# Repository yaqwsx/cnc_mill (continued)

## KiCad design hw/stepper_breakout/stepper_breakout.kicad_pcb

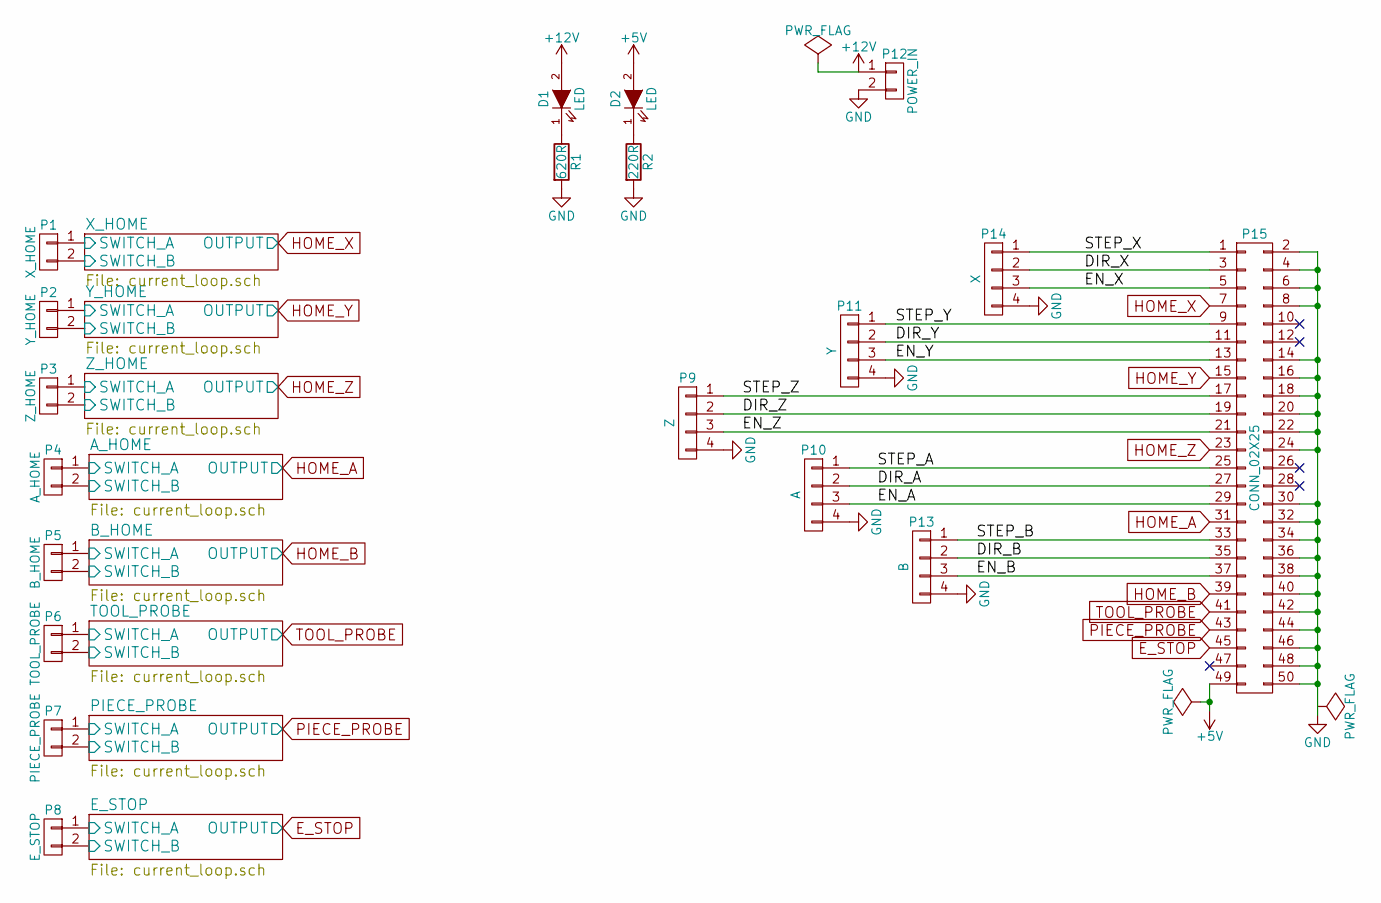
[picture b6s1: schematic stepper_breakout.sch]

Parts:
D1, D2: LED; LED_1206
P1: X_HOME; TerminalBlock_Pheonix_MKDS1.5-2pol
P2: Y_HOME; TerminalBlock_Pheonix_MKDS1.5-2pol
P3: Z_HOME; TerminalBlock_Pheonix_MKDS1.5-2pol
P4: A_HOME; TerminalBlock_Pheonix_MKDS1.5-2pol
P5: B_HOME; TerminalBlock_Pheonix_MKDS1.5-2pol
P6: TOOL_PROBE; TerminalBlock_Pheonix_MKDS1.5-2pol
P7: PIECE_PROBE; TerminalBlock_Pheonix_MKDS1.5-2pol
P8: E_STOP; TerminalBlock_Pheonix_MKDS1.5-2pol
P9: Z; TerminalBlock_Pheonix_MKDS1.5-4pol
P10: A; TerminalBlock_Pheonix_MKDS1.5-4pol
P11: Y; TerminalBlock_Pheonix_MKDS1.5-4pol
P12: POWER_IN; TerminalBlock_Pheonix_MKDS1.5-2pol
P13: B; TerminalBlock_Pheonix_MKDS1.5-4pol
P14: X; TerminalBlock_Pheonix_MKDS1.5-4pol
P15: CONN_02X25; IDC_Header_Straight_50pins
R1: 620R; R_0603
R2: 220R; R_0603

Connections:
+5V: D2.2 (A), P15.49
+12V: D1.2 (A), P12.1; also elsewhere on the board
/A_HOME/SWITCH_A: P4.1; also elsewhere on the board
/A_HOME/SWITCH_B: P4.2; also elsewhere on the board
/B_HOME/SWITCH_A: P5.1; also elsewhere on the board
/B_HOME/SWITCH_B: P5.2; also elsewhere on the board
/DIR_A: P10.2, P15.27
/DIR_B: P13.2, P15.35
/DIR_X: P14.2, P15.3
/DIR_Y: P11.2, P15.11
/DIR_Z: P9.2, P15.19
/EN_A: P10.3, P15.29
/EN_B: P13.3, P15.37
/EN_X: P14.3, P15.5
/EN_Y: P11.3, P15.13
/EN_Z: P9.3, P15.21
/E_STOP/SWITCH_A: P8.1; also elsewhere on the board
/E_STOP/SWITCH_B: P8.2; also elsewhere on the board
/PIECE_PROBE/SWITCH_A: P7.1; also elsewhere on the board
/PIECE_PROBE/SWITCH_B: P7.2; also elsewhere on the board
/STEP_A: P10.1, P15.25
/STEP_B: P13.1, P15.33
/STEP_X: P14.1, P15.1
/STEP_Y: P11.1, P15.9
/STEP_Z: P9.1, P15.17
/TOOL_PROBE/SWITCH_A: P6.1; also elsewhere on the board
/TOOL_PROBE/SWITCH_B: P6.2; also elsewhere on the board
/X_HOME/SWITCH_A: P1.1; also elsewhere on the board
/X_HOME/SWITCH_B: P1.2; also elsewhere on the board
/Y_HOME/SWITCH_A: P2.1; also elsewhere on the board
/Y_HOME/SWITCH_B: P2.2; also elsewhere on the board
/Z_HOME/SWITCH_A: P3.1; also elsewhere on the board
/Z_HOME/SWITCH_B: P3.2; also elsewhere on the board
E_STOP: P15.45; also elsewhere on the board
GND: P9.4, P10.4, P11.4, P12.2, P13.4, P14.4, P15.2, P15.4, P15.6, P15.8, P15.14, P15.16, P15.18, P15.20, P15.22, P15.24, P15.30, P15.32, P15.34, P15.36, P15.38, P15.40, P15.42, P15.44, P15.46, P15.48, P15.50, R1.2, R2.2; also elsewhere on the board
HOME_A: P15.31; also elsewhere on the board
HOME_B: P15.39; also elsewhere on the board
HOME_X: P15.7; also elsewhere on the board
HOME_Y: P15.15; also elsewhere on the board
HOME_Z: P15.23; also elsewhere on the board
unnamed: D1.1 (K), R1.1
unnamed: D2.1 (K), R2.1
PIECE_PROBE: P15.43; also elsewhere on the board
TOOL_PROBE: P15.41; also elsewhere on the board

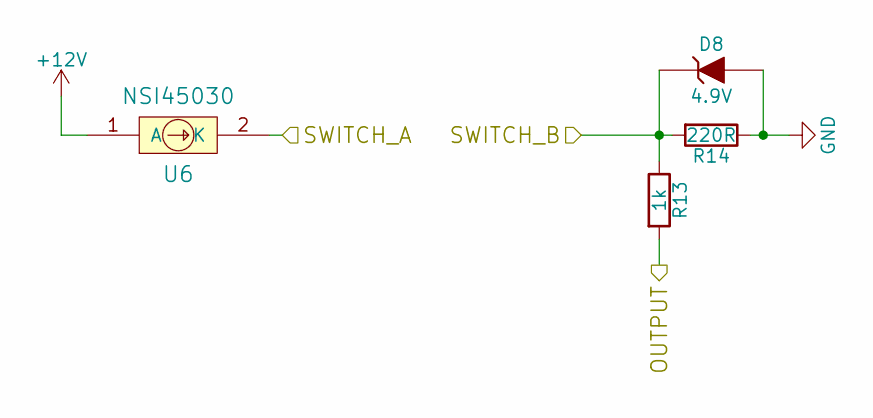
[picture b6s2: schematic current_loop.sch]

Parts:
D3: 4.9V; MELF_Standard
R3: 1k; R_0603_HandSoldering
R4: 220R; R_0603_HandSoldering
U1: NSI45030; SOD-123

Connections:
+12V: U1.1 (A); also elsewhere on the board
/Y_HOME/SWITCH_A: U1.2 (K); also elsewhere on the board
/Y_HOME/SWITCH_B: D3.1 (K), R3.1, R4.2; also elsewhere on the board
GND: D3.2 (A), R4.1; also elsewhere on the board
HOME_Y: R3.2; also elsewhere on the board

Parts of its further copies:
D4, D5, D6, D7, D8, D9, D10: 4.9V; MELF_Standard
R5, R7, R9, R11, R13, R15, R17: 1k; R_0603_HandSoldering
R6, R8, R10, R12, R14, R16, R18: 220R; R_0603_HandSoldering
U2, U3, U4, U5, U6, U7, U8: NSI45030; SOD-123

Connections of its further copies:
+12V: U2.1 (A), U3.1 (A), U4.1 (A), U5.1 (A), U6.1 (A), U7.1 (A), U8.1 (A); also elsewhere on the board
/A_HOME/SWITCH_A: U3.2 (K); also elsewhere on the board
/A_HOME/SWITCH_B: D5.1 (K), R7.1, R8.2; also elsewhere on the board
/B_HOME/SWITCH_A: U4.2 (K); also elsewhere on the board
/B_HOME/SWITCH_B: D6.1 (K), R9.1, R10.2; also elsewhere on the board
/E_STOP/SWITCH_A: U7.2 (K); also elsewhere on the board
/E_STOP/SWITCH_B: D9.1 (K), R15.1, R16.2; also elsewhere on the board
/PIECE_PROBE/SWITCH_A: U6.2 (K); also elsewhere on the board
/PIECE_PROBE/SWITCH_B: D8.1 (K), R13.1, R14.2; also elsewhere on the board
/TOOL_PROBE/SWITCH_A: U5.2 (K); also elsewhere on the board
/TOOL_PROBE/SWITCH_B: D7.1 (K), R11.1, R12.2; also elsewhere on the board
/X_HOME/SWITCH_A: U8.2 (K); also elsewhere on the board
/X_HOME/SWITCH_B: D10.1 (K), R17.1, R18.2; also elsewhere on the board
/Z_HOME/SWITCH_A: U2.2 (K); also elsewhere on the board
/Z_HOME/SWITCH_B: D4.1 (K), R5.1, R6.2; also elsewhere on the board
E_STOP: R15.2; also elsewhere on the board
GND: D4.2 (A), D5.2 (A), D6.2 (A), D7.2 (A), D8.2 (A), D9.2 (A), D10.2 (A), R6.1, R8.1, R10.1, R12.1, R14.1, R16.1, R18.1; also elsewhere on the board
HOME_A: R7.2; also elsewhere on the board
HOME_B: R9.2; also elsewhere on the board
HOME_X: R17.2; also elsewhere on the board
HOME_Z: R5.2; also elsewhere on the board
PIECE_PROBE: R13.2; also elsewhere on the board
TOOL_PROBE: R11.2; also elsewhere on the board

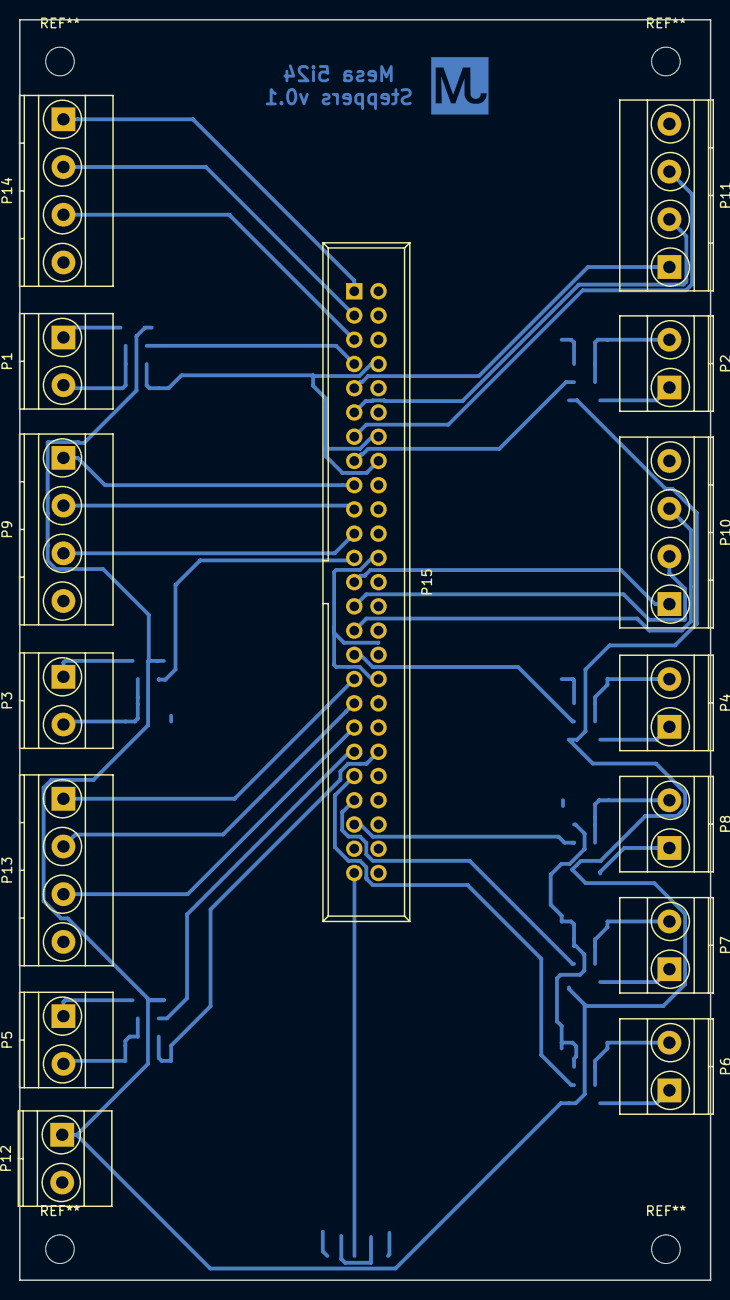
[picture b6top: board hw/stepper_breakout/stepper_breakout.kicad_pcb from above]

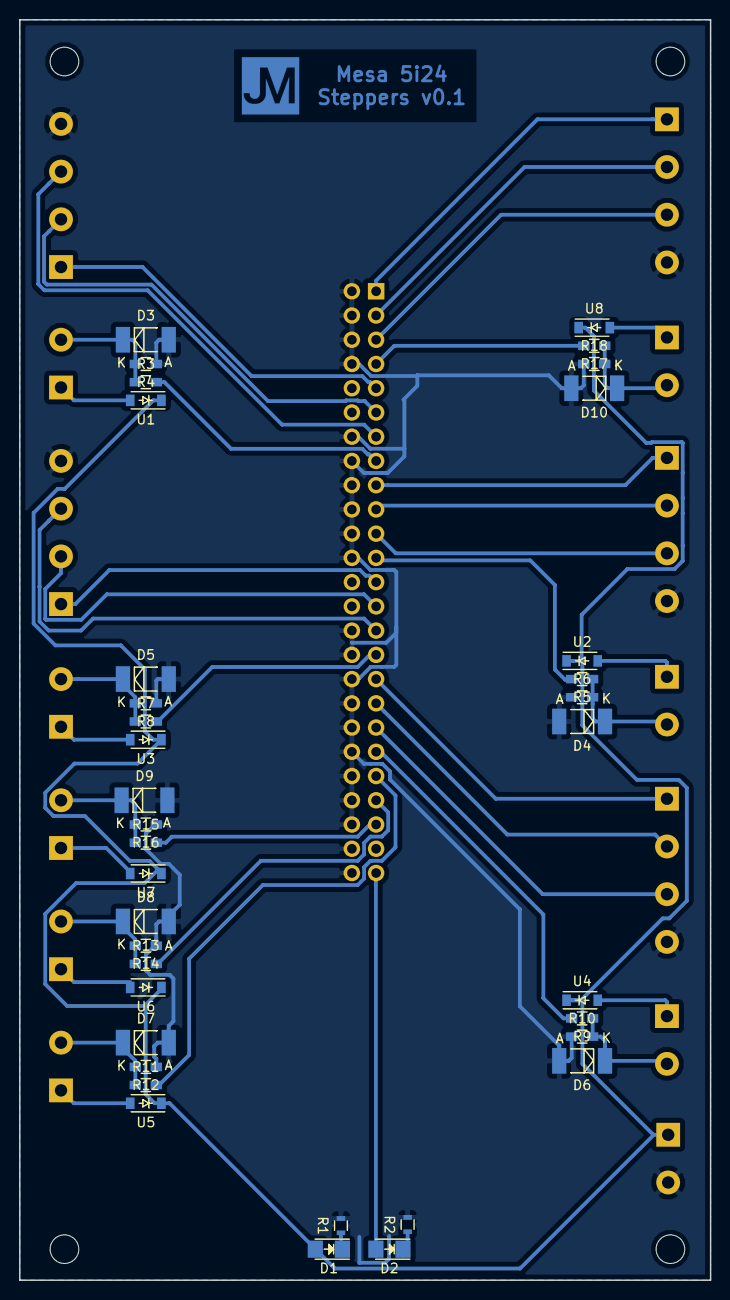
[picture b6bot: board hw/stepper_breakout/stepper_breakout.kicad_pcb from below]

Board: 2 copper layers, 72.4 x 132.1 mm, 51 parts (36 on the bottom side), 44 nets.

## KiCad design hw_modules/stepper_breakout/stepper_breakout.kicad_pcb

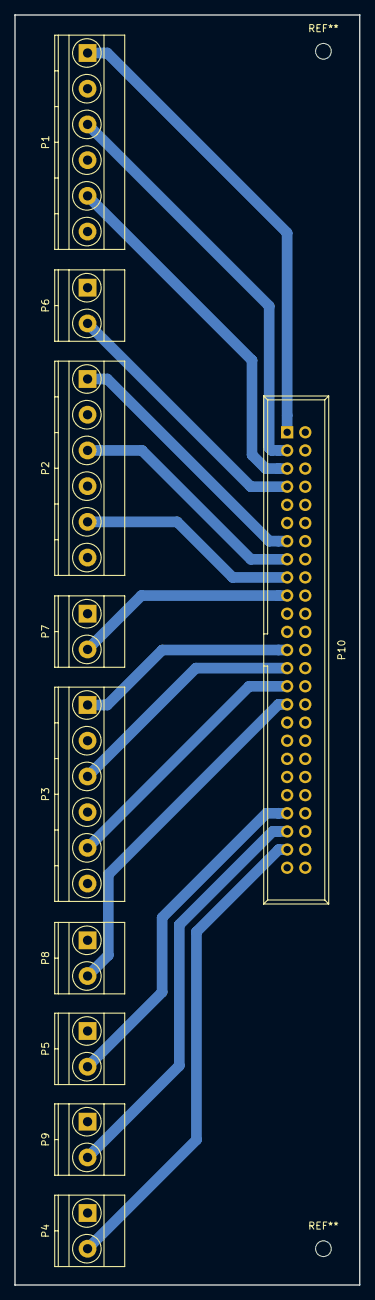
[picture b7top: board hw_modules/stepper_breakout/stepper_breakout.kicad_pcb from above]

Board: 2 copper layers, 48.3 x 177.8 mm, 10 parts (0 on the bottom side), 16 nets.

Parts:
P1, P2, P3: CONN_01X06; TerminalBlock_Pheonix_MKDS1.5-6pol
P4, P5, P6, P7, P8, P9: CONN_01X02; TerminalBlock_Pheonix_MKDS1.5-2pol
P10: CONN_02X25; IDC_Header_Straight_50pins

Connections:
DIR_X: P1.3, P10.3
DIR_Y: P2.3, P10.15
DIR_Z: P3.3, P10.27
ENA_X: P1.5, P10.5
ENA_Y: P2.5, P10.17
ENA_Z: P3.5, P10.29
ESTOP_IN: P4.2, P10.47
ESTOP_OUT: P9.2, P10.45
GND: P1.2, P1.4, P1.6, P2.2, P2.4, P2.6, P3.2, P3.4, P3.6, P4.1, P5.1, P6.1, P7.1, P8.1, P9.1, P10.2, P10.4, P10.6, P10.8, P10.10, P10.12, P10.14, P10.16, P10.18, P10.20, P10.22, P10.24, P10.26, P10.28, P10.30, P10.32, P10.34, P10.36, P10.38, P10.40, P10.42, P10.44, P10.46, P10.48, P10.50
HOME_X: P6.2, P10.7
HOME_Y: P7.2, P10.19
HOME_Z: P8.2, P10.31
PROBE_IN: P5.2, P10.43
STEP_X: P1.1, P10.1
STEP_Y: P2.1, P10.13
STEP_Z: P3.1, P10.25

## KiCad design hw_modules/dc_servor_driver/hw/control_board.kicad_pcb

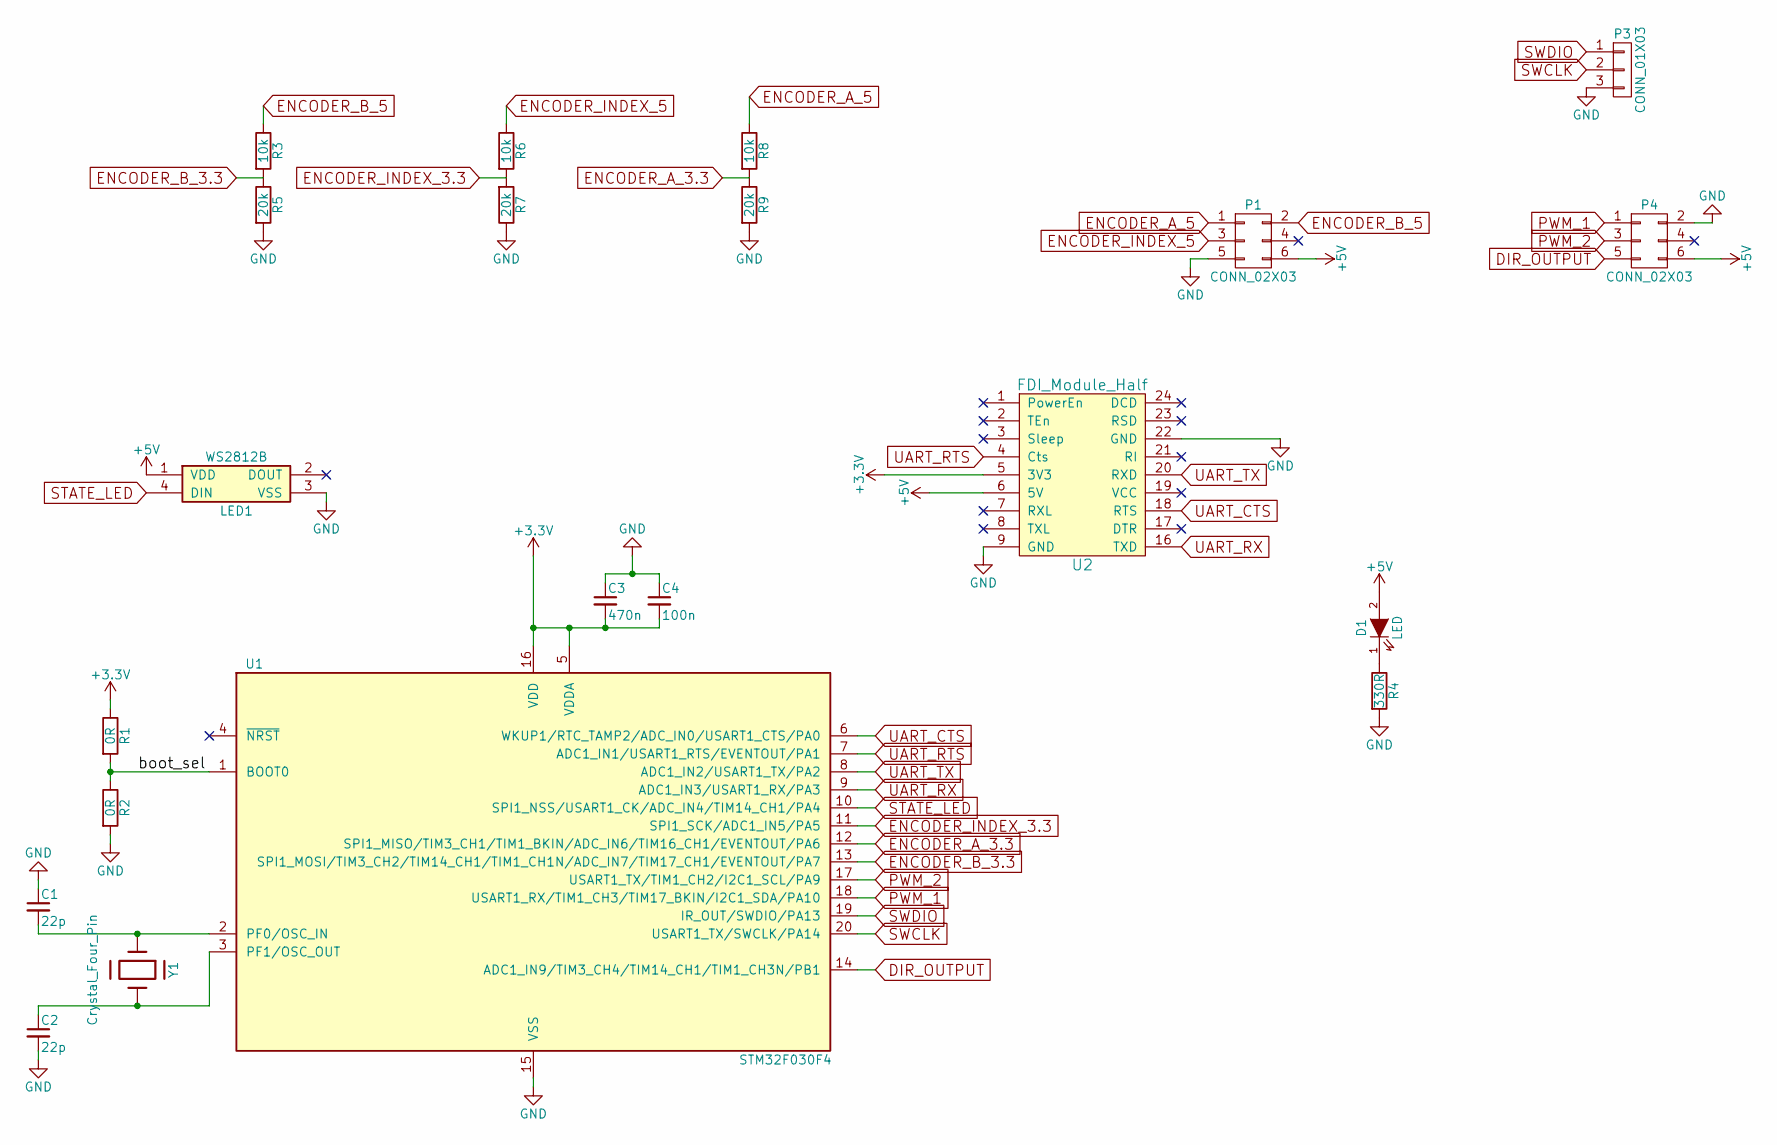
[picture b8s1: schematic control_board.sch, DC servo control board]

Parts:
C1, C2: 22p; C_0603
C3: 470n; C_0603
C4: 100n; C_0603
D1: LED; LED_0603
LED1: WS2812B; LED_PLCC4-WS2812B
P1, P4: CONN_02X03; Pin_Header_Straight_2x03
P3: CONN_01X03; Pin_Header_Straight_1x03
R1, R2: 0R; R_0603
R3, R6, R8: 10k; R_0603
R4: 330R; R_0603
R5, R7, R9: 20k; R_0603
U1: STM32F030F4; TSSOP-20_4.4x6.5mm_Pitch0.65mm
U2: FDI_Module_Half; FTDI_Half
Y1: Crystal_Four_Pin; Crystal_SMD_0603_4Pads

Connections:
+3V3: C3.2, C4.2, R1.1, U1.5 (VDDA), U1.16 (VDD), U2.5 (3V3)
+5V: D1.2 (A), LED1.1 (VDD), P1.6, P4.6, U2.6 (5V)
/boot_sel: R1.2, R2.1, U1.1 (BOOT0)
DIR_OUTPUT: P4.5, U1.14 (ADC1_IN9/TIM3_CH4/TIM14_CH1/TIM1_CH3N/P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)
ENCODER_A_3.3: R8.2, R9.1, U1.12 (SPI1_MISO/TIM3_CH1/TIM1_BKIN/ADC_IN6/TI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)
ENCODER_A_5: P1.1, R8.1
ENCODER_B_3.3: R3.2, R5.1, U1.13 (SPI1_MOSI/TIM3_CH2/TIM14_CH1/TIM1_CH1N/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)
ENCODER_B_5: P1.2, R3.1
ENCODER_INDEX_3.3: R6.2, R7.2, U1.11 (SPI1_SCK/ADC1_IN5/PA5)
ENCODER_INDEX_5: P1.3, R6.1
GND: C1.1, C2.2, C3.1, C4.1, LED1.3 (VSS), P1.5, P3.3, P4.2, R2.2, R4.2, R5.2, R7.1, R9.2, U1.15 (VSS), U2.9 (GND), U2.22 (GND), Y1.2 (GND), Y1.4 (GND)
unnamed: C1.2, U1.2 (PF0/OSC_IN), Y1.1
unnamed: C2.1, U1.3 (PF1/OSC_OUT), Y1.3
unnamed: D1.1 (K), R4.1
PWM_1: P4.1, U1.18 (USART1_RX/TIM1_CH3/TIM17_BKIN/I2C1_SDA/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)
PWM_2: P4.3, U1.17 (USART1_TX/TIM1_CH2/I2C1_SCL/PA9)
STATE_LED: LED1.4 (DIN), U1.10 (SPI1_NSS/USART1_CK/ADC_IN4/TIM14_CH1/PA4)
SWCLK: P3.2, U1.20 (USART1_TX/SWCLK/PA14)
SWDIO: P3.1, U1.19 (IR_OUT/SWDIO/PA13)
UART_CTS: U1.6 (WKUP1/RTC_TAMP2/ADC_IN0/USART1_CTS/PA0), U2.18 (RTS)
UART_RTS: U1.7 (ADC1_IN1/USART1_RTS/EVENTOUT/PA1), U2.4 (Cts)
UART_RX: U1.9 (ADC1_IN3/USART1_RX/PA3), U2.16 (TXD)
UART_TX: U1.8 (ADC1_IN2/USART1_TX/PA2), U2.20 (RXD)

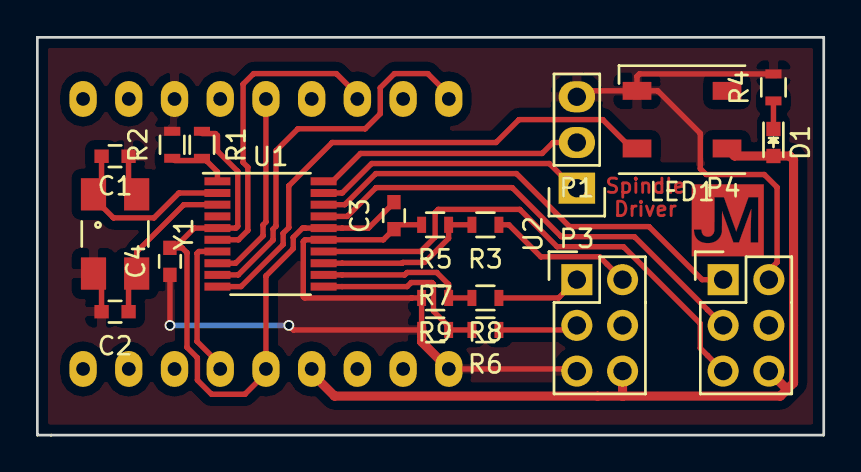
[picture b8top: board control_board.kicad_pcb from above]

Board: 2 copper layers, 43.7 x 22.1 mm, 21 parts (0 on the bottom side), 23 nets.

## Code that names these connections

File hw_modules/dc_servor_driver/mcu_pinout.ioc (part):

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Mcu.Name=STM32F030F4Px
Mcu.Package=TSSOP20
Mcu.UserName=STM32F030F4Px
PA0.Mode=CTS_RTS
PA0.Signal=USART1_CTS
PA1.Mode=CTS_RTS
PA1.Signal=USART1_RTS
PA10.Signal=S_TIM1_CH3
PA13.Mode=Serial-WireDebug
PA13.Signal=SYS_SWDIO
PA14.Mode=Serial-WireDebug
PA14.Signal=SYS_SWCLK
PA2.Mode=Asynchronous
PA2.Signal=USART1_TX
PA3.Mode=Asynchronous
PA3.Signal=USART1_RX
PA5.GPIOParameters=GPIO_Label
PA5.GPIO_Label=ENCODER_INDEX
PA5.Signal=GPXTI5
PA6.Signal=S_TIM3_CH1
PA7.Signal=S_TIM3_CH2
PA9.Signal=S_TIM1_CH2
PB1.GPIOParameters=GPIO_Label
PB1.GPIO_Label=DIR_OUTPUT
PB1.Signal=GPIO_Output
PF0-OSC_IN.Mode=HSE-External-Oscillator
PF0-OSC_IN.Signal=RCC_OSC_IN
PF1-OSC_OUT.Mode=HSE-External-Oscillator
PF1-OSC_OUT.Signal=RCC_OSC_OUT

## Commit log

2015-12-29 Initial working commit
2015-12-29 Add deploy script, clean examples and fix attributes
2015-12-29 Handle incomplete data in temp HAL module
2016-01-01 New iteration
    - add tool length touch of macro
    - change pedant mode to vposition
    - fix Y jogging direction
2016-01-17 First verion of new spindle control HW
2016-01-21 Firt verision of dc_servo_driver board
2016-01-23 Add new toolchange, add variable spindle ratio
2016-01-23 Change Y motor driver & max speeds to avoid resonance
2016-02-07 Indroduce tool length probe
2016-02-20 New macro for position saving
2016-03-26 Add first configuration with Mesa 6i24
2016-03-26 Add spindle light
2016-08-03 Add missing files for spindle light
2016-08-03 Add work-in-progress dc servo driver
2016-08-03 Add "old" (currenty used) DC servo driver
2016-08-03 Add stepper breakout for Mesa 5i24
2016-08-07 Initial commit of overall electrical connection
2016-10-30 Add 5i24 stepper breakout
2016-11-06 Add Spindle&GPIO breakout
2016-11-06 Adjust track width in stepper breakout
2016-11-07 Add power board
2016-11-20 Tweak power and breakout boards a little
2016-11-20 Add labels for breakout and power boards
2016-11-20 Add wire connection schematics
2018-08-26 Add new spindle light
2018-12-28 Add spindle H bridge
2019-01-08 Add PWM to -+10V board
2019-01-20 Add new configuration with the new spindle control
2019-01-20 Remove old configurations
2023-02-25 Add 3rd pot
2024-05-04 Add Fusion postprocessor
